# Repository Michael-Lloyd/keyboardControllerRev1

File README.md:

# friendly-keyboard

This project stems from a (much delayed) collaborative project with a friend from work. It's a bluetooth enabled keyboard, that functions similarly to the logitech MX keys, but with much more, and less problems. The end goal is to provide him the design, but between those steps I've found ways to make improvements over common design choices. 

## Links 

Blog: [Link](https://micl.dev/pcbs/friendly-keyboard)

Hackaday: [Link](https://hackaday.io/project/187157-friendly-keyboard)

## Features (Controller)

* USB-C Interface for Charging + Wired Operation
* USB 3.2 onboard Hub controller (with device mode toggle) 
* USB PD Power delivery with configurable battery settings 
* 1-6 Cell Lithium-ion battery management 
* USB to SPI direct comm bus via USB controller 
* I2C, SPI or diode matrix bus keyboard configuration compatibility 
* QMK Ported firmware w/ distributed handlers (configurable) 
* 16MBytes user flash 
* Low power BLE Mesh sleep compatibility 
* User chosen BLE/Wireless Antenna via U.FL Connector 

## Design 

## Changelog

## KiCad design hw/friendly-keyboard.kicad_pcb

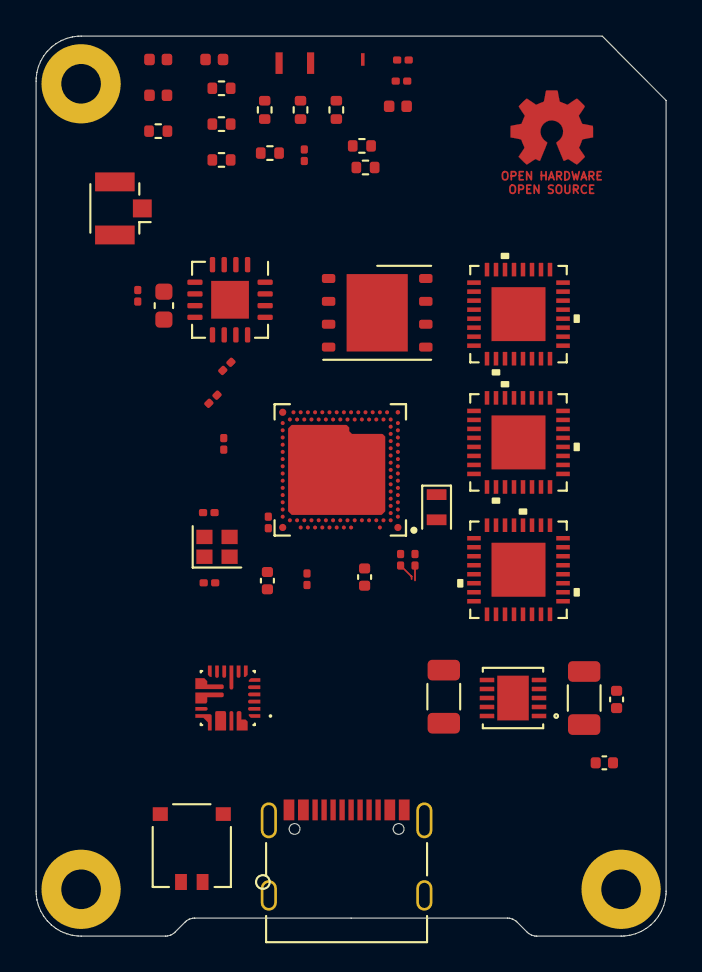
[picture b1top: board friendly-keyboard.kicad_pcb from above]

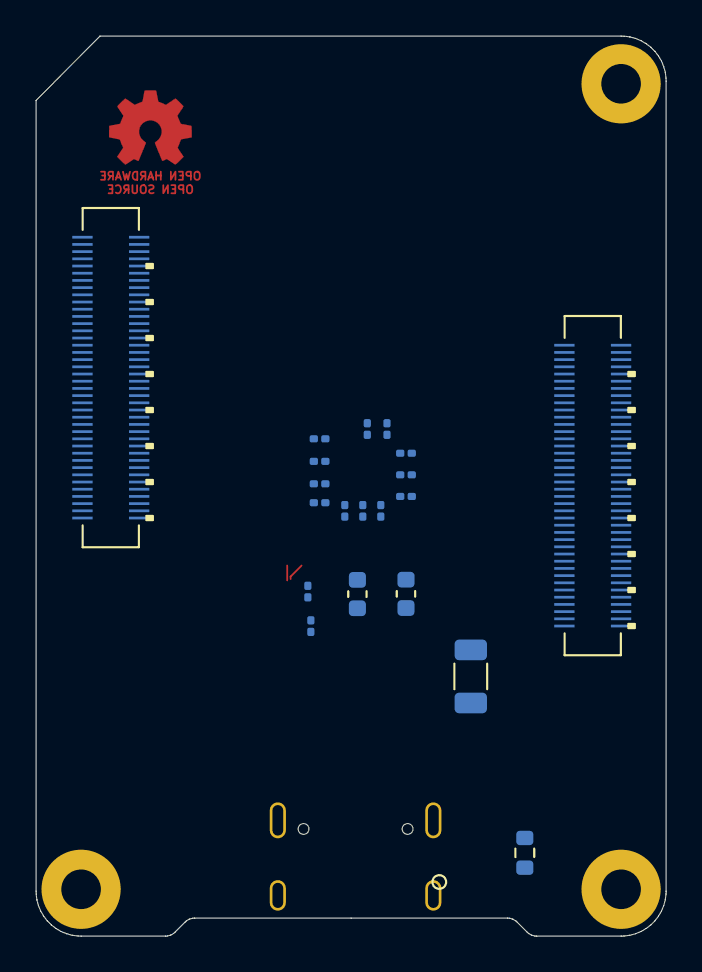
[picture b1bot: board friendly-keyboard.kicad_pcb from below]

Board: 6 copper layers, 35.0 x 50.0 mm, 72 parts (20 on the bottom side), 26 nets.

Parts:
AE1: Antenna_Chip; RF-ANT_A1001312
C1: 1pF; C_0201_0603Metric
C2, C14, C15, C16, C17, C18, C19, C20, C21, C22, C23, C24, C25, C26, C32, C33: 100nF; C_0201_0603Metric
C3: 10μF; C_0603_1608Metric
C4, C5: 1.2pF; C_0201_0603Metric
C6, C10: 10pF; C_0402_1005Metric
C8, C9: 10μF; C_1206_3216Metric
C11: 22μF; C_1206_3216Metric
C27, C28: C; C_0201_0603Metric
C29, C34: 2.2nF; C_0201_0603Metric
C30: 4.7μF; C_0402_1005Metric
C31: C; C_0402_1005Metric
C35: 0.7pF; C_0201_0603Metric
C36: DNP; C_0201_0603Metric
FB1: FerriteBead; R_0603_1608Metric
H1: H1; MountingHole_2.2mm_M2_Pad
H2: H3; MountingHole_2.2mm_M2_Pad
H4: H4; MountingHole_2.2mm_M2_Pad
J1: Conn_Coaxial; U.FL_Hirose_U.FL-R-SMT-1_Vertical
J2: Conn_01x02; DF57H-2P-1-2V-21
J3: USB_C_Receptacle_USB2.0; USB_C_Receptacle_Palconn_UTC16-G
J4, J5: Left Mezzanine; DF40C-80DS-0-4V-51
L1, L2: 1.9nH; L_0402_1005Metric
L3: 4.7nH; L_0402_1005Metric
L5, L6: 10uH; L_0603_1608Metric
L7: 2.2nH; L_0402_1005Metric
R1: DNP; R_0402_1005Metric
R2: 0Ω; R_0402_1005Metric
R3, R4, R5, R6, R7, R8, R9, R10: R; R_0402_1005Metric
R18, R19: 28Ω; R_0201_0603Metric
TIE1: FL; NetTie_RF_FL
U1: NRF21540-QDAA-R; QFN-16-1EP_4x4mm_P0.65mm_EP2.1x2.1mm
U2: LTC3411AEDD
U3: MAX77751CEFG+
U4: NRF5340-QKAA-R7
U5: W25Q32JVZP; W25QJVZP
U6, U7, U8: PCAL6524; PCAL6524HEHP
Y1: 32MHz-ECS-320-8-37B2-7KM-TR; Crystal_SMD_2016-4Pin_2.0x1.6mm
Y2: 32.768kHz; Crystal_SMD_TXC_9HT11-2Pin_2.0x1.2mm

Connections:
+3.3V: C6.2, C10.2, C11.1, C31.1, U5.8 (VCC)
+5.0V: C8.1, C9.1, U2.6 (PV_{IN})
/Microcontroller/Power Inputs/VDD_USB: U4.A5 (VBUS), U4.E1 (VDDH), U4.J1 (DCCH), U4.L1 (VDD3)
/Microcontroller/Power Inputs/VDD_nRF: C19.1, C20.1, C21.1, C22.1, C23.1, C24.1, C25.1, C26.1, U4.B8 (VDD2)
/Microcontroller/RF Interface/ANT: C35.1, L7.1
DGND: C19.2, C20.2, C21.2, C22.2, C23.2, C24.2, C25.2, C26.2, C27.2, C28.2, C31.2, U5.4 (GND), U5.9 (EP), Y1.2, Y1.4
GND: C2.2, C3.2
unnamed: AE1.1 (FEED), R3.1, R3.2, R4.1, R4.2, R5.1, R5.2, R6.1, R6.2, R7.1, R7.2, R8.1, R8.2, R9.1, R9.2, R10.1, R10.2, TIE1.2
unnamed: AE1.2 (PCB_Trace), TIE1.1
unnamed: C4.2, L1.2, L3.1, R1.1, R2.1
unnamed: C29.1, L5.1, Y2.1
unnamed: C5.2, J1.1 (In), L2.2
unnamed: FB1.1, J3.S1 (SHIELD)
unnamed: C6.1, C10.1, U2.9 (V_{FB})
unnamed: C27.1, U4.C31 (XC1), Y1.1
unnamed: C28.1, U4.B30 (XC2), Y1.3
unnamed: U6.25 (VSS), U6.EPAD (VSS)
unnamed: U7.25 (VSS), U7.EPAD (VSS)
unnamed: U8.25 (VSS), U8.EPAD (VSS)
PGND: C8.2, C9.2, C11.2, FB1.2, J3.A1 (GND), J3.A12 (GND), J3.B1 (GND), J3.B12 (GND), U2.2 (SYNC/MODE), U2.3 (SGND), U2.5 (PGND), U3.18 (PGND)
RF_LINE: C1.1, C36.1, L7.2
USB_+: J3.A6 (D+), J3.B6 (D+)
USB_-: J3.A7 (D-), J3.B7 (D-)
VDD: C2.1, C3.1, C14.1, C15.1, C16.1, C17.1, C18.1, U1.5 (VDD), U1.6 (VDD), U4.AC1 (VDD), U4.AG1 (VDD), U4.AJ31 (VDD), U4.AL3 (VDD), U4.AL7 (VDD), U4.AL11 (VDD), U4.AL17 (VDD), U4.AL25 (VDD), U4.B28 (VDD), U4.C1 (VDD), U4.E31 (VDD), U4.N31 (VDD), U4.U1 (VDD)
VSS: U1.1 (VSS), U1.16 (VSS), U1.17 (VSS), U4.104 (VSS), U4.A25 (VSS), U4.B12 (VSS), U4.B26 (VSS), U4.G1 (VSS), U4.H2 (VSS), U4.J31 (VSS)
VUSB: J3.A4 (VBUS), J3.A9 (VBUS), J3.B4 (VBUS), J3.B9 (VBUS)

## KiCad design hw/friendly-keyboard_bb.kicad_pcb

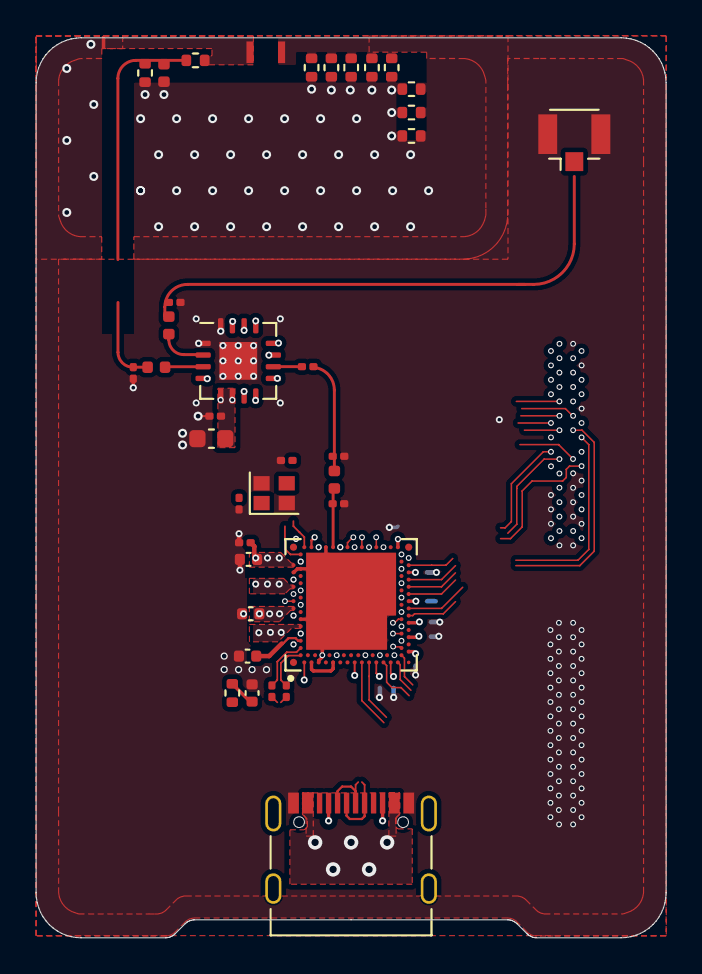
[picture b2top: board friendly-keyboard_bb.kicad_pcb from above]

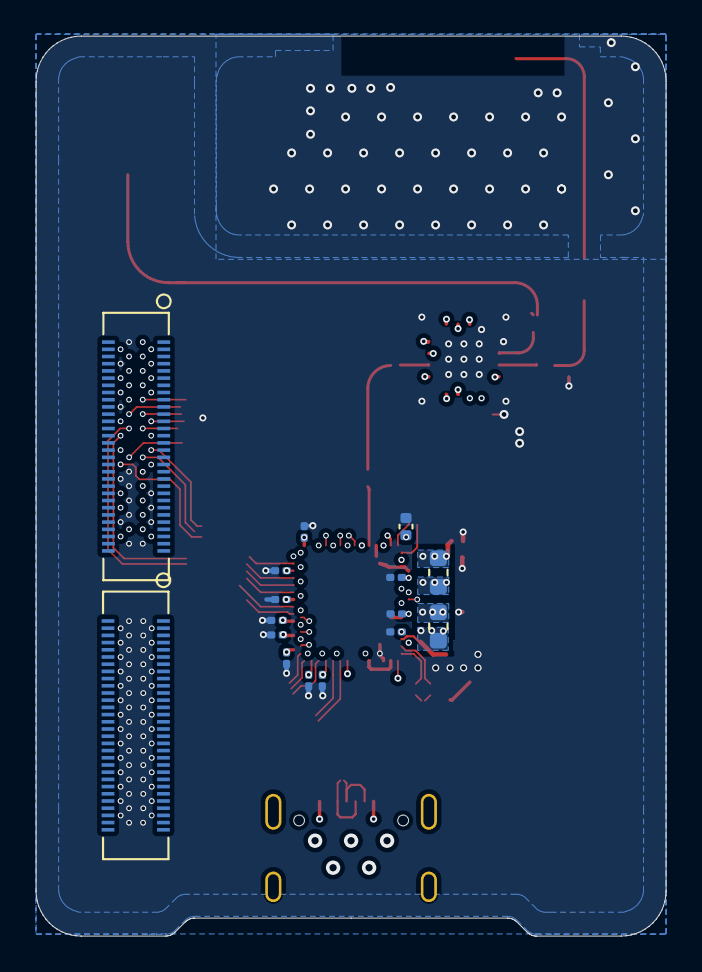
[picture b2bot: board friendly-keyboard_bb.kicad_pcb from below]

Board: 6 copper layers, 35.0 x 50.0 mm, 54 parts (16 on the bottom side), 28 nets.

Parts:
AE1: Antenna_Chip; RF-ANT_A1001312
C3, C20, C21, C22, C23, C24, C25, C26, C27, C37, C38: 100nF; C_0201_0603Metric
C4: 10µF; C_0603_1608Metric
C5, C6: 1.2pF; C_0201_0603Metric
C15: 1pF; C_0201_0603Metric
C28, C29, C34: 1µF; C_0402_1005Metric
C30, C33: 2.2nF; C_0201_0603Metric
C31: 0.7pF; C_0201_0603Metric
C32: DNP; C_0201_0603Metric
C35, C36: 4.7µF; C_0402_1005Metric
C39, C40: C; C_0201_0603Metric
J1: Conn_Coaxial; U.FL_Hirose_U.FL-R-SMT-1_Vertical
J2: USB_C_Receptacle_USB2.0; USB_C_Receptacle_Palconn_UTC16-G
J3, J4: Conn_02x30_Odd_Even; DF40HC-4-0-60DS-0-4V-51
L1, L4: 1.9nH; L_0402_1005Metric
L3: 4.7nH; L_0402_1005Metric
L6, L8: 10µH; L_0603_1608Metric
L7: 2.2nH; L_0402_1005Metric
R1: 0Ω; R_0402_1005Metric
R2, R3, R4, R20, R21, R22, R23, R24: R; R_0402_1005Metric
R5: 2.2Ω; R_0402_1005Metric
R6, R7: 28Ω; R_0201_0603Metric
R19: DNP; R_0402_1005Metric
TIE1: FL; NetTie_RF_FL
U3: NRF21540-QDAA-R; QFN-16-1EP_4x4mm_P0.65mm_EP2.1x2.1mm
U4: NRF5340-QKAA-R7
Y1: 32MHz-ECS-320-8-37B2-7KM-TR

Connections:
/ANT1_OUT: L1.1, U3.2 (ANT1)
/ANT2_OUT: L4.1, U3.3 (ANT2)
/nrf_D+: R7.2, U4.B2 (D+)
/nrf_D-: R6.2, U4.B4 (D-)
GND: AE1.1 (FEED), C3.2, C4.2, C5.1, C6.1, C20.2, C21.2, C22.2, C23.2, C24.2, C25.2, C26.2, C27.2, C28.2, C29.2, C30.2, C31.2, C32.2, C33.2, C34.2, C35.2, C36.2, C37.2, C38.2, C39.2, C40.2, J1.2 (Ext), J2.A1 (GND), J2.A12 (GND), J2.B1 (GND), J2.B12 (GND), L3.2, R2.1, R2.2, R3.1, R3.2, R4.1, R4.2, R19.2, R20.1, R20.2, R21.1, R21.2, R22.1, R22.2, R23.1, R23.2, R24.1, R24.2, TIE1.2, U3.1 (VSS), U3.16 (VSS), U3.17 (VSS), U4.104 (VSS), U4.A25 (VSS), U4.B12 (VSS), U4.B26 (VSS), U4.G1 (VSS), U4.H2 (VSS), U4.J31 (VSS), Y1.2, Y1.4
unnamed: AE1.2 (PCB_Trace), R1.2, TIE1.1
unnamed: C5.2, L1.2, L3.1, R1.1, R19.1
unnamed: C6.2, J1.1 (In), L4.2
unnamed: C15.2, U3.10 (TRX)
unnamed: C28.1, U4.A19 (VDD1)
unnamed: C29.1, C30.1, L6.1, U4.A27 (DECR), U4.G31 (DECRF)
unnamed: C31.1, L7.1, U4.L31 (ANT)
unnamed: C33.1, U4.B8 (VDD2)
unnamed: C34.1, L8.1, U4.A15 (DECD)
unnamed: C35.1, R5.2, U4.A5 (VBUS)
unnamed: C36.1, U4.B6 (DECUSB)
unnamed: C37.1, U4.A23 (DECN)
unnamed: C38.1, U4.A13 (DECA)
unnamed: C39.1, U4.B30 (XC2), Y1.1
unnamed: C40.1, U4.C31 (XC1), Y1.3
unnamed: L6.2, U4.A21 (DCC)
unnamed: L8.2, U4.B10 (DCCD)
unnamed: U4.E1 (VDDH), U4.L1 (VDD3)
RF_LINE: C15.1, C32.1, L7.2
USB_+: J2.A6 (D+), J2.B6 (D+), R7.1
USB_-: J2.A7 (D-), J2.B7 (D-), R6.1
VBUS: J2.A4 (VBUS), J2.A9 (VBUS), J2.B4 (VBUS), J2.B9 (VBUS), R5.1
VDD: C3.1, C4.1, C20.1, C21.1, C22.1, C23.1, C24.1, C25.1, C26.1, C27.1, U3.5 (VDD), U3.6 (VDD), U4.AC1 (VDD), U4.AG1 (VDD), U4.AJ31 (VDD), U4.AL3 (VDD), U4.AL7 (VDD), U4.AL11 (VDD), U4.AL17 (VDD), U4.AL25 (VDD), U4.B28 (VDD), U4.C1 (VDD), U4.E31 (VDD), U4.N31 (VDD), U4.U1 (VDD)

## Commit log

2022-09-07 qmk port
2022-09-07 qmk port (Files linked to zombie submodule
2022-09-07 Removed old qmk git dir
2022-09-13 Lost too many chips ):. Restarting from scratch
2022-09-13 nrf side system diagram
2022-09-13 Xtal calculator
2022-09-13 Xtal values
2022-09-13 NOR Flash
2022-09-13 Cypress USB interface symbol & Layout needs fixing
2022-09-13 Fixed symbol
2022-09-13 Messed up system layout, consumer from receptacle, datasheet uses left to right
2022-09-13 System sketch
2022-09-13 MAX77751CEFG+ Symbol fix
2022-12-20 lolz
